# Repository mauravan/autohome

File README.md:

# autohome

Home Assistant companion firmware for battery-powered ESP32-C3 CO₂ / temperature / humidity sensor nodes with an e-paper display.

## What this is

- ESPHome project built on ESP-IDF, targeting the `esp32-c3-devkitm-1`.
- Each node wakes on a timer, takes one SCD41 single-shot measurement, refreshes a WeAct e-paper display, publishes the reading, then deep-sleeps.
- Two transport families:
  - **WiFi + MQTT** with Home Assistant discovery.
  - **BLE BTHome** advertisement (WiFi stays off on timer wakes).

## Repository layout

```
INVENTORY.md          Hardware inventory
SENSORS.md            Sensor/module catalog
AGENTS.md             Detailed architecture and development guidelines
firmware/co2-node/    ESPHome project, components, tools and runbook
```

See [`firmware/co2-node/README.md`](firmware/co2-node/README.md) for flashing, MQTT verification, troubleshooting and power notes.

## Quick start

```bash
pip install esphome
cd firmware/co2-node
cp secrets.yaml.example secrets.yaml   # fill in mqtt_* and ota_password
esphome config top.yaml
esphome run top.yaml --device /dev/ttyACM0
```

For BLE builds use `top-ble.yaml`, `mid-ble.yaml`, etc. instead.

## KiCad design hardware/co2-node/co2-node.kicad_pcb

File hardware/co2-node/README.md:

# CO2 sensor node — custom production board (rev A)

2-layer, 95 × 45 mm, 1.6 mm, ENIG. No development components.
KiCad-native project: open `co2-node.kicad_pro`. Regenerate with
`python3 tools/gen_all.py` — never hand-edit generated files.
Gates: `python3 tools/verify_all.py` (ERC 0 errors, DRC parity 0 +
unconnected-only pre-route, netlist assertions, exports, firmware).

## Electrical-equivalence rule (binding)

This board MUST reproduce the dev wiring in
`firmware/co2-node/README.md` with identical pin functions and polarities.
Any change to the table below is a **rev B**: firmware and layout both
depend on it.

## Frozen pin map (rev A)

| Signal | ESP32-C3-MINI-1 pin | Net | Firmware reference |
|---|---|---|---|
| SCD41 SDA | GPIO1 | `I2C_SDA` | `i2c.sda` |
| SCD41 SCL | GPIO21 | `I2C_SCL` | `i2c.scl` |
| EPD MOSI | GPIO6 | `EPD_SDA` | `spi.mosi_pin` |
| EPD SCK | GPIO4 | `EPD_SCL` | `spi.clk_pin` |
| EPD CS | GPIO7 | `EPD_CS` | `cs_pin` |
| EPD DC | GPIO5 | `EPD_DC` | `dc_pin` |
| EPD RST | GPIO0 | `EPD_RES` | `reset_pin` |
| EPD BUSY | GPIO10 | `EPD_BUSY` | `busy_pin` |
| Battery sense | GPIO3 (ADC1_CH3) | `VBAT_SENSE` | `adc.pin`, `multiply: 2.0` |
| Peripheral power | GPIO20 | `PWR_EN` | `switch.gpio`, HIGH = P3V3 on |
| USB D− / D+ | GPIO18 / GPIO19 | `USB_DM` / `USB_DP` | native USB CDC |
| BOOT | GPIO9 | `BOOT_N` | button to GND, 10k pull-up |
| Reset | EN | `RESET_N` | button to GND, 10k pull-up + 100 nF |

- GPIO2/GPIO8: strapping, 10k pull-ups, no functions.
- GPIO20/21 are UART0 pins; ROM boot chatter is harmless. Logger stays on
  native USB (GPIO18/19). No UART header.
- Power gate is **active-high** with a 100k pull-down on GPIO20 so P3V3 is
  off during deep sleep. Firmware re-asserts HIGH + 1 s settle every wake.
- Battery divider is **VBAT/2** (1 M/1 M) so `multiply: 2.0` and the SoC
  table in `co2-node-common.yaml` stay valid.

## Sheets

| Sheet | Content |
|---|---|
| `power` | USB-C → 0.75 A polyfuse → USBLC6 → BQ24074 (500 mA) → VSYS; holder → 2 A polyfuse → Q2 reverse P-FET → DW01A/FS8205A → BAT+; VSYS → TPS7A26 → 3V3; 3V3 → Q3/Q4 gate → P3V3; BAT+ → 1 M/1 M → 100 nF → 1 k → GPIO3 |
| `mcu` | ESP32-C3-MINI-1-N4, 10 µF + 1 µF + 0.1 µF, EN pull-up/cap, BOOT/RESET buttons, USB 22 Ω + ESD, test pads, fiducials |
| `sensor` | SCD41-D-R2, VDD/VDDH tied, DNC floating pad, 10k pull-ups to P3V3, ferrite + 10 µF, 1 µF at sensor, no pour under body |
| `display` | FPC-24 0.5 mm + WeAct boost transcribed from `reference/` (3V3-fed, no ME6216A33), 100 Ω series, E_BS = 4-line SPI |
| `connectors` | 18650 holder, NTC, test pads, mounting holes, label ref |

## Copy-critical references (`reference/`)

- `WeAct-EpaperModule-SchDoc.pdf` — the boost + connector block is copied,
  not redrawn from memory. `WeAct-SchDoc-text.txt` is a machine dump;
  `weact-transcription.md` is the audited netlist used for `display`.
- `SCD4x-Datasheet.pdf` — §2.3/§4.2 land pattern: pads VDD, VDDH, GND, SDA,
  SCL, DNC. VDD+VDDH tied at sensor + 1 µF; DNC soldered to a **floating**
  pad (never GND); no SEL pin; 10k pull-ups to P3V3; low-noise rail
  (ferrite + 10 µF).
- `ESP32-C3-MINI-1-Datasheet.pdf` — module pin numbers (§3.1), strapping
  (GPIO2/8/9), 15 mm antenna keepout (§11).
- `WeAct-SSD1681-Datasheet.pdf` — controller init reference.

## Layout constraints

- AISLER 2-layer rules: 0.2 mm min trace/space, 0.3 mm min drill,
  0.6 mm min via pad.
- Antenna overhangs the top edge; no copper/battery/metal within 15 mm,
  both layers; plastic case only.
- SCD41 at bottom-front edge by the vent grille; no copper pour under body;
  charger/LDO/boost away from sensor; cell holder top edge at y = 15 mm.
- Test pads TP1–8 on bottom edge y = 1.5 (pogo row, clear of holder).
  `3V3 GND BAT+ P3V3 RESET_N BOOT_N I2C_SCL PWR_EN`, 1.0 mm.
- Adopted connector footprints: USB-C =
  `Connector_USB:USB_C_Receptacle_HCTL_HC-TYPE-C-16P-01A` (MPN HCTL
  `HC-TYPE-C-16P-01A`), FPC-24 =
  `Connector_FFC-FPC:Hirose_FH12-24S-0.5SH_1x24-1MP_P0.50mm_Horizontal`,
  switches = KMR2 (`KMR221G`), mounting = plated 2.7 mm M2.5 to GND.
- Net naming: the single USB data-minus net is `USB_DM` (`USB_DN` retired).

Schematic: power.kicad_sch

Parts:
BT1: Keystone-1043; MPN 1043
C20, C24: 1u; C_0603_1608Metric; MPN CL10B105KP8NNNC
C21, C22, C25, C27: 10u; C_0603_1608Metric; MPN CL10A106KP8NNNC
C23, C26, C28: 0.1u; C_0603_1608Metric; MPN CL10B104KP8NNNC
C29: 100n; C_0603_1608Metric; MPN CL10B104KP8NNNC
D1: USBLC6-2SC6; SOT-23-6; MPN USBLC6-2SC6
D20: CHG-GRN; LED_0603_1608Metric; MPN LTST-C190KGKT
F1: 0.75A; Fuse_0603_1608Metric; MPN MF-PSMF075X-2
F2: 2A; Fuse_1206_3216Metric; MPN MF-PSMF200X-2
J1: USB-C-16P; USB_C_Receptacle_HCTL_HC-TYPE-C-16P-01A; MPN TYPE-C-16P
Q2, Q3: AO3401A; SOT-23; MPN AO3401A
Q4: BSS138; SOT-23; MPN BSS138
R10, R11: 5.1k; R_0603_1608Metric; MPN RC0603-5.1k-1%
R12, R13: 22R; R_0603_1608Metric; MPN RC0603-22R-1%
R20: 1.78k; R_0603_1608Metric; MPN RC0603-1.78k-1%
R21: DNP; R_0603_1608Metric; not fitted
R22: 2.2k; R_0603_1608Metric; MPN RC0603-2.2k-1%
R23: 10k; R_0603_1608Metric; MPN RC0603-10k-1%
R24: 100R; R_0603_1608Metric; MPN RC0603-100R-1%
R25, R32: 1k; R_0603_1608Metric; MPN RC0603-1k-1%
R27, R28, R29: 100k; R_0603_1608Metric; MPN RC0603-100k-1%
R30, R31: 1M; R_0603_1608Metric; MPN RC0603-1M-1%
U1: BQ24074RGTR; BQ24074-VQFN-16; MPN BQ24074RGTR
U2: TPS7A2633DRVR; TPS7A26-WSON-6; MPN TPS7A2633DRVR
U3: DW01A; SOT-23-6; MPN DW01A
U4: FS8205A; TSSOP-8_4.4x3mm_P0.65mm; MPN FS8205A

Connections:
3V3: C25.1, C26.1, Q3.2 (S), R22.1, R23.1, R27.1, R28.1, U2.1 (OUT); also elsewhere on the board
BAT+: C21.1, R30.1, U1.2 (BAT), U1.3 (BAT); also elsewhere on the board
BAT_RAW: Q2.3 (D), R24.1
BAT_SENSE_RAW: C29.1, R30.2, R31.1, R32.1
CELL+: BT1.1 (+), F2.1
CELL_F: F2.2, Q2.2 (S)
CHG_STAT: D20.1 (K), R22.2, U1.9 (CHG)
DW_OC: U3.3 (OC), U4.5 (G2)
DW_OD: U3.1 (OD), U4.4 (G1)
DW_VCC: C23.1, R24.2, U3.5 (VCC)
DW_VM: R25.1, U3.2 (CS)
GND: BT1.2 (-), C20.2, C21.2, C22.2, C23.2, C24.2, C25.2, C26.2, C27.2, C28.2, C29.2, D1.2 (GND), D20.2 (A), J1.A1 (GND), J1.A12 (GND), J1.B1 (GND), J1.B12 (GND), J1.SH, Q2.1 (G), Q4.2 (S), R10.2, R11.2, R20.2, R21.2, R29.2, R31.2, U1.4 (CE), U1.5 (EN2), U1.8 (VSS), U1.17 (EP), U2.2 (NC), U2.5 (GND), U2.7 (EP), U3.6 (GND), U4.3 (S1), U4.6 (S2); also elsewhere on the board
ILIM: R21.1, U1.12 (ILIM)
ISET_MON: R20.1, U1.16 (ISET)
NC_ITERM: U1.15 (ITERM)
NC_SBU: J1.A8 (SBU1), J1.B8 (SBU2)
NC_TD: U3.4 (TD)
NC_TMR: U1.14 (TMR)
P3V3: C27.1, C28.1, Q3.3 (D); also elsewhere on the board
PACK-: R25.2, U4.1 (D12), U4.2 (S1), U4.7 (S2), U4.8 (D12)
PG_3V3: R27.2, U2.3 (PG)
PG_STAT: R23.2, U1.7 (PGOOD)
PWR_EN: Q4.1 (G), R29.1; also elsewhere on the board
Q3_G: Q3.1 (G), Q4.3 (D), R28.2
TS_NTC: U1.1 (TS); also elsewhere on the board
USB_CC1: J1.A5 (CC1), R10.1
USB_CC2: J1.B5 (CC2), R11.1
USB_DM: D1.3 (I/O2), D1.4 (I/O2), J1.A7 (D-), J1.B7 (D-), R13.1, R13.2; also elsewhere on the board
USB_DP: D1.1 (I/O1), D1.6 (I/O1), J1.A6 (D+), J1.B6 (D+), R12.1, R12.2; also elsewhere on the board
VBAT_SENSE: R32.2; also elsewhere on the board
VBUS: C20.1, D1.5 (VCC), F1.1, F1.2, J1.A4 (VBUS), J1.A9 (VBUS), J1.B4 (VBUS), J1.B9 (VBUS), U1.6 (EN1), U1.13 (IN)
VSYS: C22.1, C24.1, U1.10 (OUT), U1.11 (OUT), U2.4 (EN), U2.6 (IN)

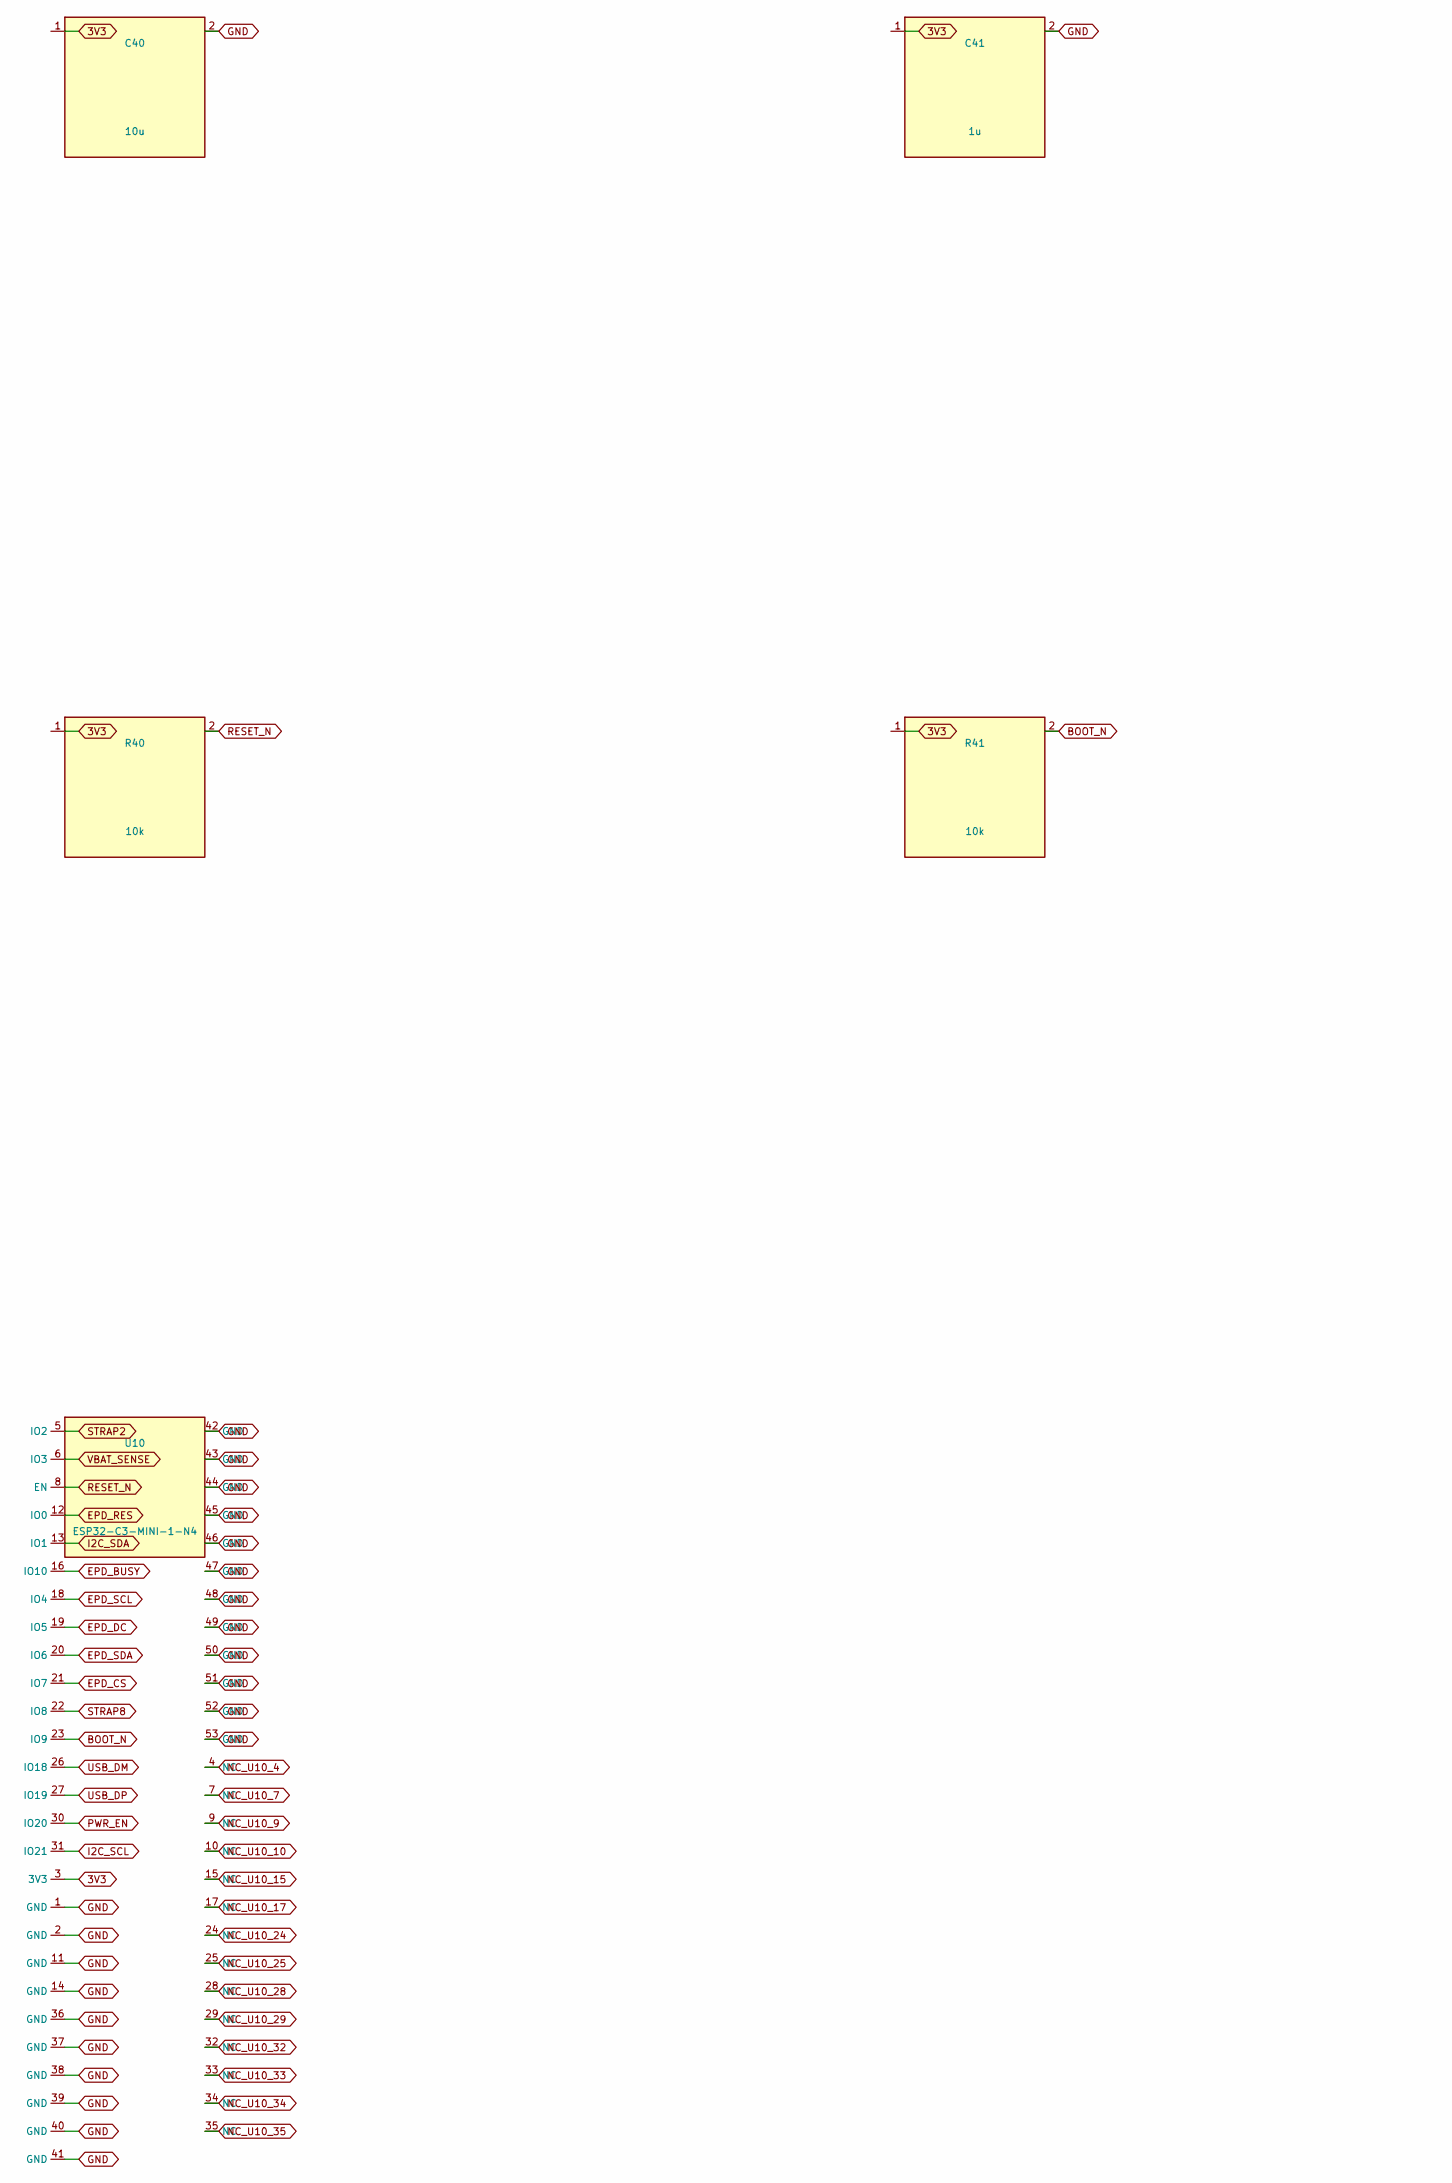
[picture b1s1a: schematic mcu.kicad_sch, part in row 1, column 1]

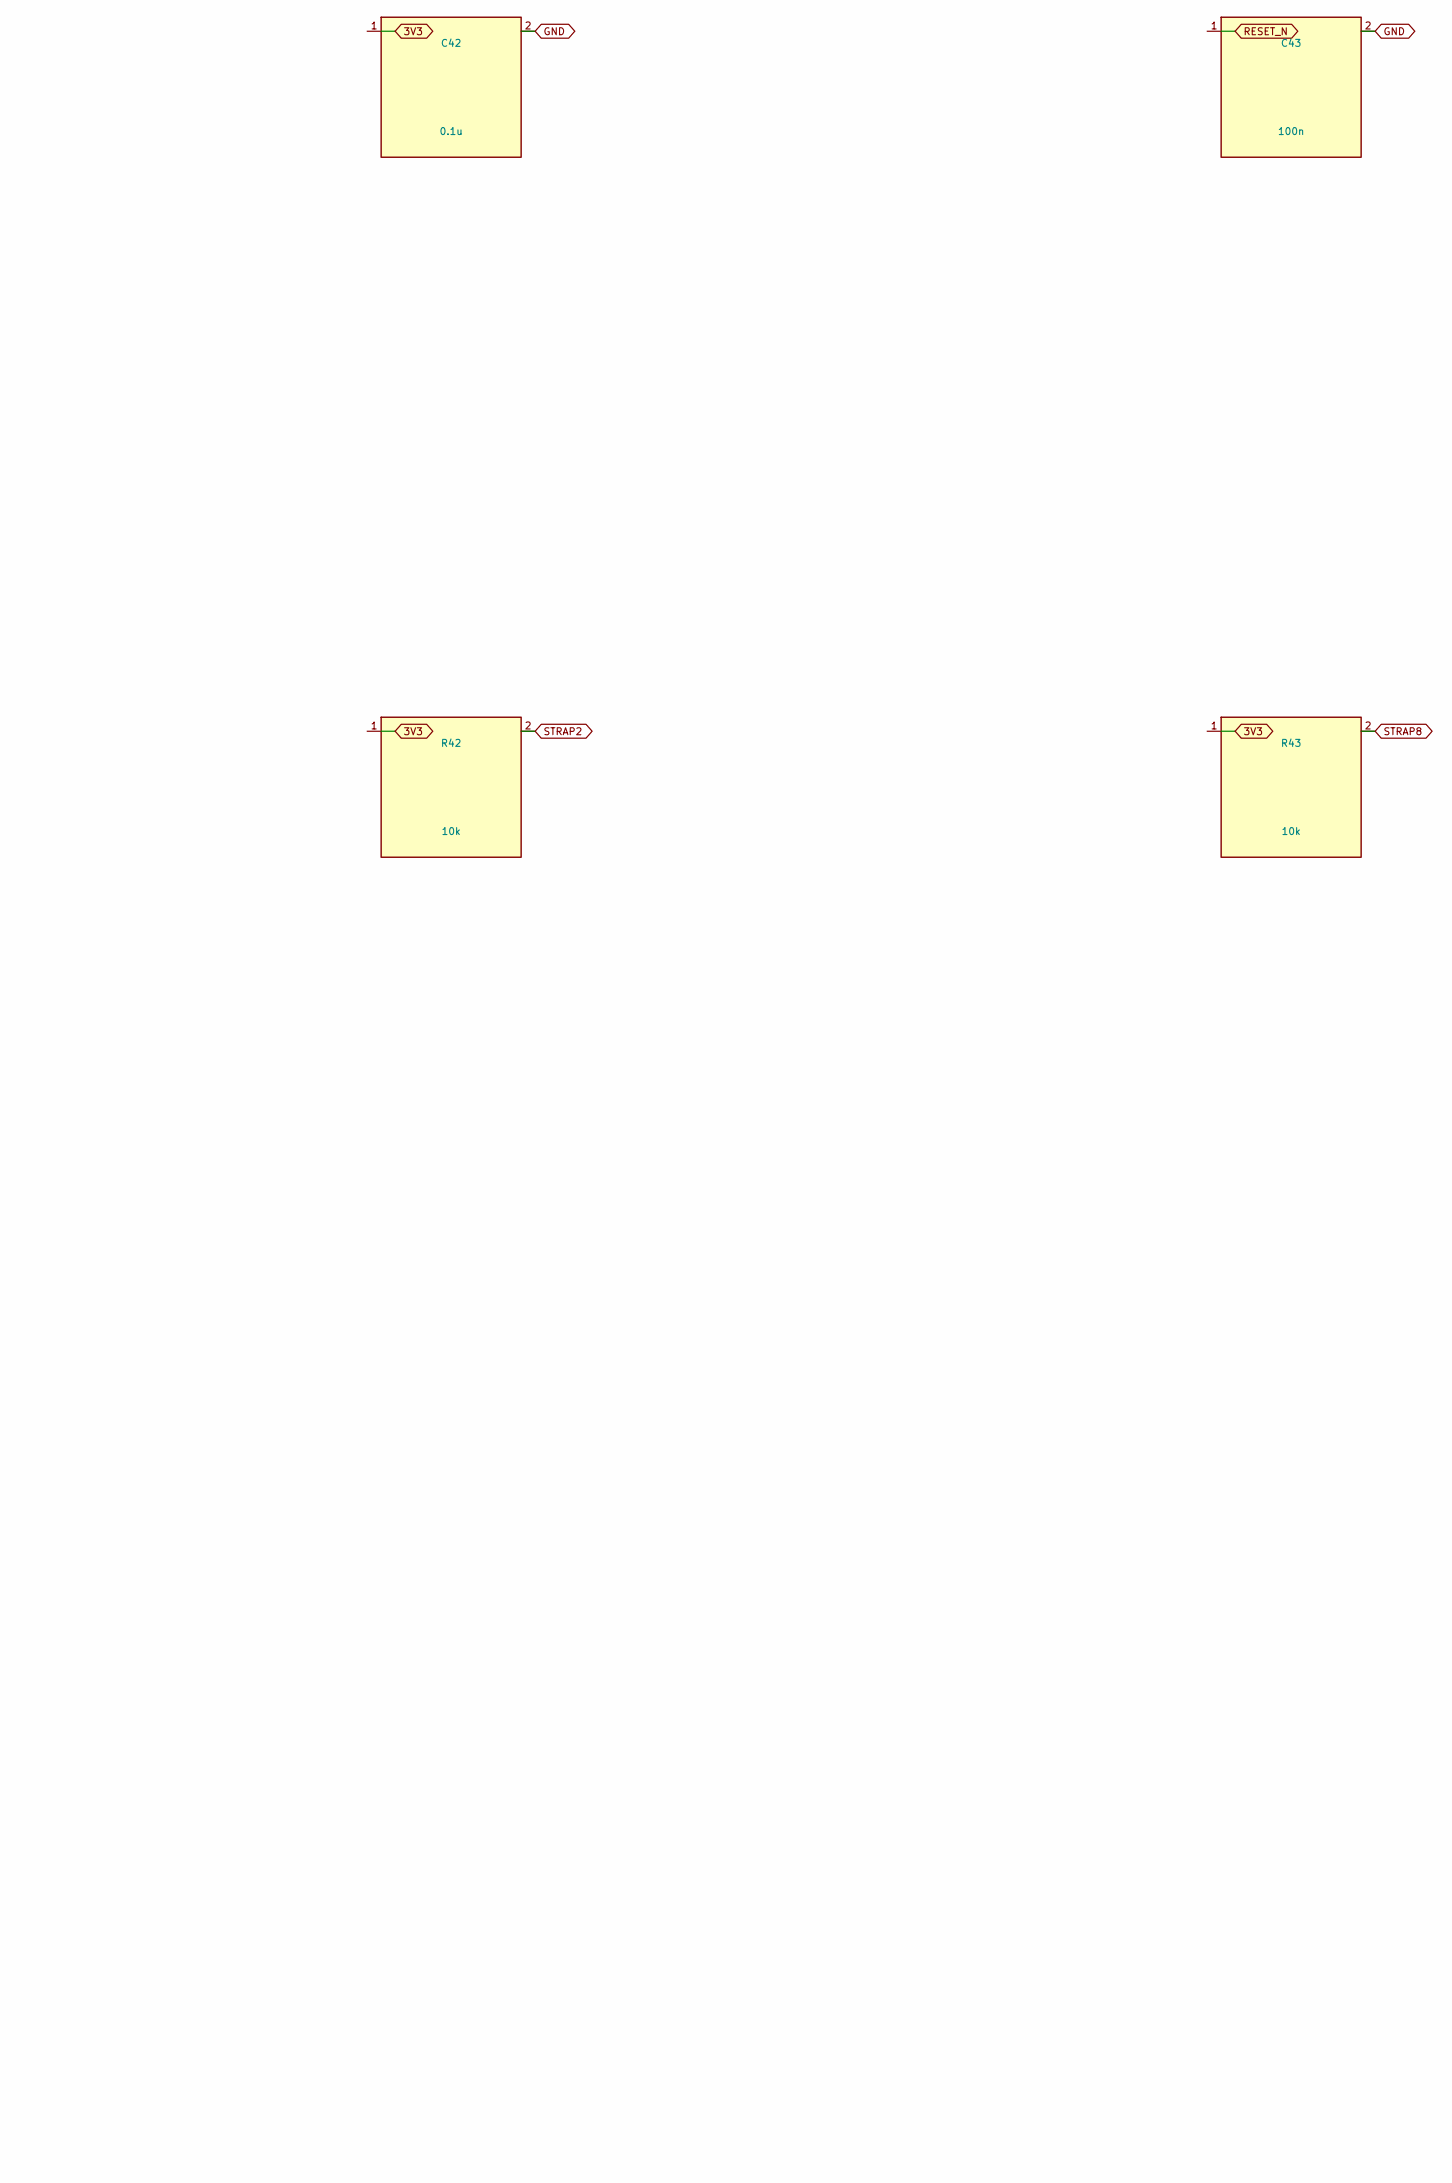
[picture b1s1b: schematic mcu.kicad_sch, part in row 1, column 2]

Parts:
C40: 10u; C_0603_1608Metric; MPN CL10A106KP8NNNC
C41: 1u; C_0603_1608Metric; MPN CL10B105KP8NNNC
C42: 0.1u; C_0603_1608Metric; MPN CL10B104KP8NNNC
C43: 100n; C_0603_1608Metric; MPN CL10B104KP8NNNC
R40, R41, R42, R43: 10k; R_0603_1608Metric; MPN RC0603-10k-1%
U10: ESP32-C3-MINI-1-N4; ESP32-C6-MINI-1; MPN ESP32-C3-MINI-1-N4

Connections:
3V3: C40.1, C41.1, C42.1, R40.1, R41.1, R42.1, R43.1, U10.3 (3V3); also elsewhere on the board
BOOT_N: R41.2, U10.23 (IO9); also elsewhere on the board
EPD_BUSY: U10.16 (IO10); also elsewhere on the board
EPD_CS: U10.21 (IO7); also elsewhere on the board
EPD_DC: U10.19 (IO5); also elsewhere on the board
EPD_RES: U10.12 (IO0); also elsewhere on the board
EPD_SCL: U10.18 (IO4); also elsewhere on the board
EPD_SDA: U10.20 (IO6); also elsewhere on the board
GND: C40.2, C41.2, C42.2, C43.2, U10.1 (GND), U10.2 (GND), U10.11 (GND), U10.14 (GND), U10.36 (GND), U10.37 (GND), U10.38 (GND), U10.39 (GND), U10.40 (GND), U10.41 (GND), U10.42 (GND), U10.43 (GND), U10.44 (GND), U10.45 (GND), U10.46 (GND), U10.47 (GND), U10.48 (GND), U10.49 (GND), U10.50 (GND), U10.51 (GND), U10.52 (GND), U10.53 (GND); also elsewhere on the board
I2C_SCL: U10.31 (IO21); also elsewhere on the board
I2C_SDA: U10.13 (IO1); also elsewhere on the board
NC_U10_4: U10.4 (NC)
NC_U10_7: U10.7 (NC)
NC_U10_9: U10.9 (NC)
NC_U10_10: U10.10 (NC)
NC_U10_15: U10.15 (NC)
NC_U10_17: U10.17 (NC)
NC_U10_24: U10.24 (NC)
NC_U10_25: U10.25 (NC)
NC_U10_28: U10.28 (NC)
NC_U10_29: U10.29 (NC)
NC_U10_32: U10.32 (NC)
NC_U10_33: U10.33 (NC)
NC_U10_34: U10.34 (NC)
NC_U10_35: U10.35 (NC)
PWR_EN: U10.30 (IO20); also elsewhere on the board
RESET_N: C43.1, R40.2, U10.8 (EN); also elsewhere on the board
STRAP2: R42.2, U10.5 (IO2)
STRAP8: R43.2, U10.22 (IO8)
USB_DM: U10.26 (IO18); also elsewhere on the board
USB_DP: U10.27 (IO19); also elsewhere on the board
VBAT_SENSE: U10.6 (IO3); also elsewhere on the board

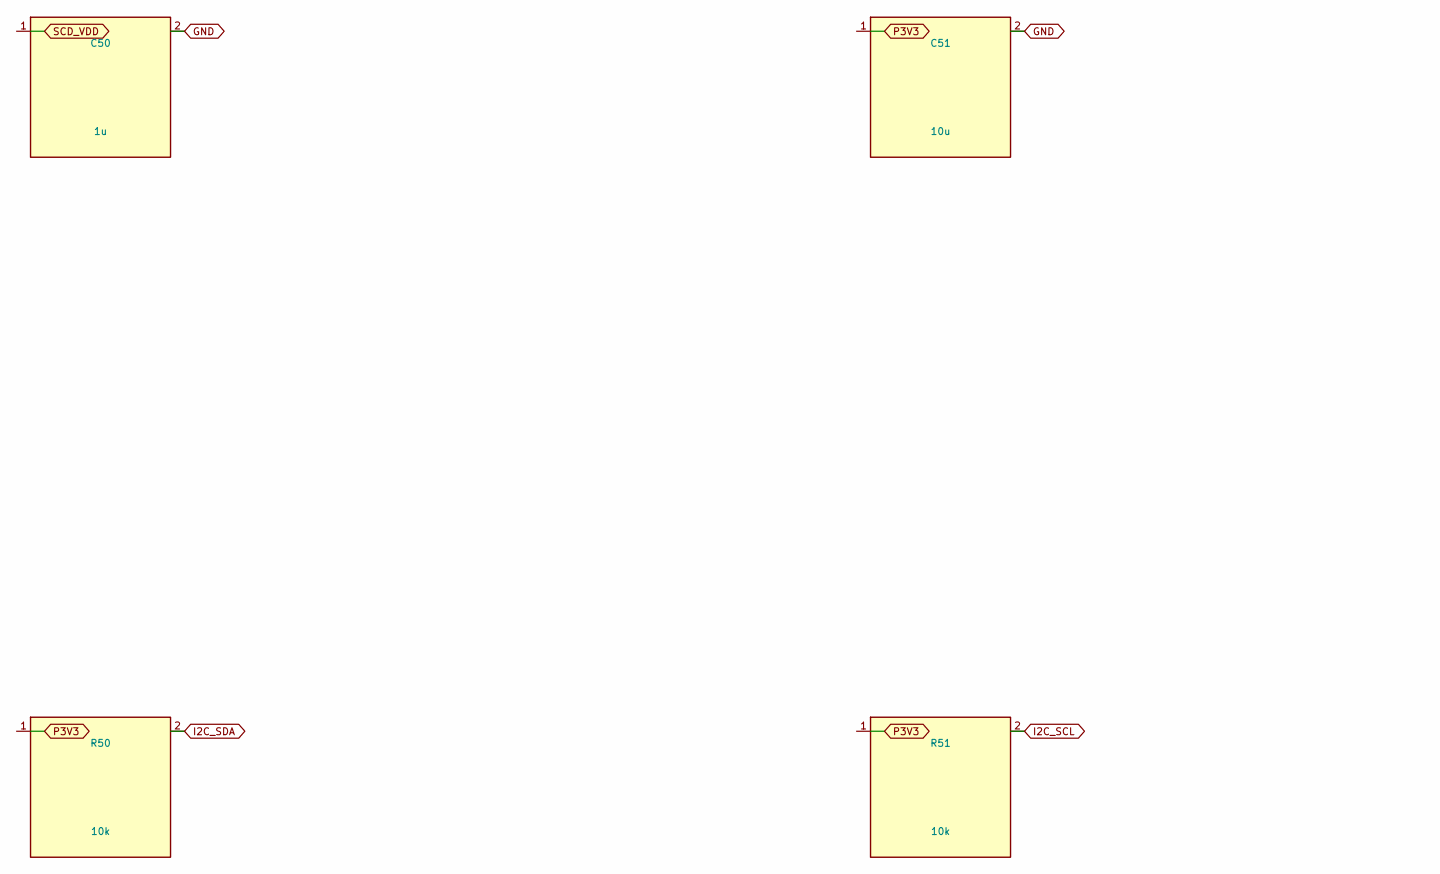
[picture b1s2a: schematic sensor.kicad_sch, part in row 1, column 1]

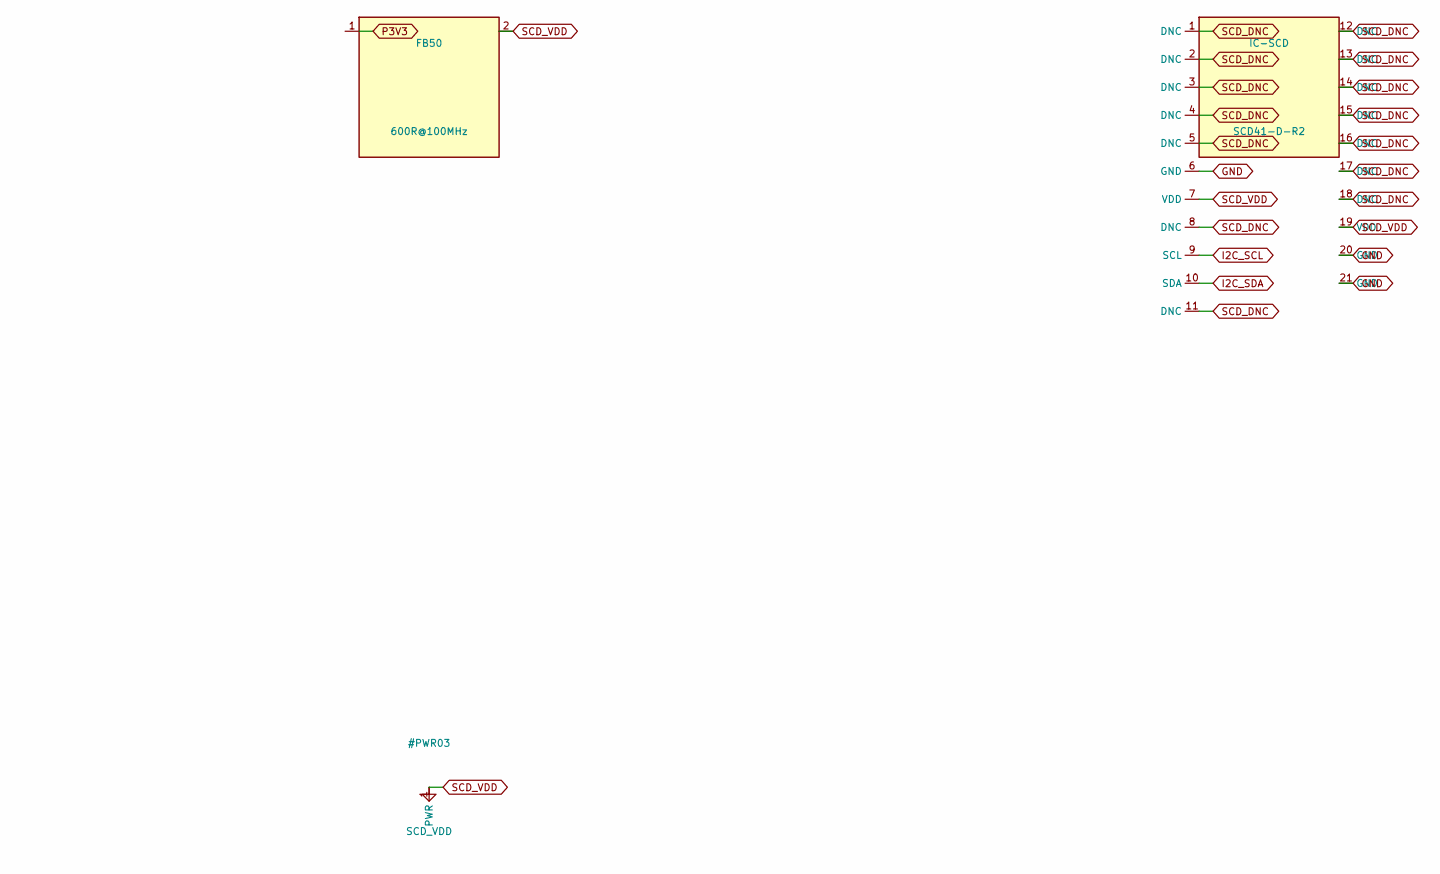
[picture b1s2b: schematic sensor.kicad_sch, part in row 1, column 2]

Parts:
C50: 1u; C_0603_1608Metric; MPN CL10B105KP8NNNC
C51: 10u; C_0603_1608Metric; MPN CL10A106KP8NNNC
FB50: 600R@100MHz; L_0603_1608Metric; MPN BLM18PG601SN1D
IC-SCD: SCD41-D-R2; Sensirion_SCD4x-1EP_10.1x10.1mm_P1.25mm_EP4.8x4.8mm; MPN SCD41-D-R2
R50, R51: 10k; R_0603_1608Metric; MPN RC0603-10k-1%

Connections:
GND: C50.2, C51.2, IC-SCD.6 (GND), IC-SCD.20 (GND), IC-SCD.21 (GND); also elsewhere on the board
I2C_SCL: IC-SCD.9 (SCL), R51.2; also elsewhere on the board
I2C_SDA: IC-SCD.10 (SDA), R50.2; also elsewhere on the board
P3V3: C51.1, FB50.1, R50.1, R51.1; also elsewhere on the board
SCD_DNC: IC-SCD.1 (DNC), IC-SCD.2 (DNC), IC-SCD.3 (DNC), IC-SCD.4 (DNC), IC-SCD.5 (DNC), IC-SCD.8 (DNC), IC-SCD.11 (DNC), IC-SCD.12 (DNC), IC-SCD.13 (DNC), IC-SCD.14 (DNC), IC-SCD.15 (DNC), IC-SCD.16 (DNC), IC-SCD.17 (DNC), IC-SCD.18 (DNC)
SCD_VDD: C50.1, FB50.2, IC-SCD.7 (VDD), IC-SCD.19 (VDD)
